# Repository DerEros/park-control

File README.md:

# park-control
A park distance control for my garage based on ESP8266

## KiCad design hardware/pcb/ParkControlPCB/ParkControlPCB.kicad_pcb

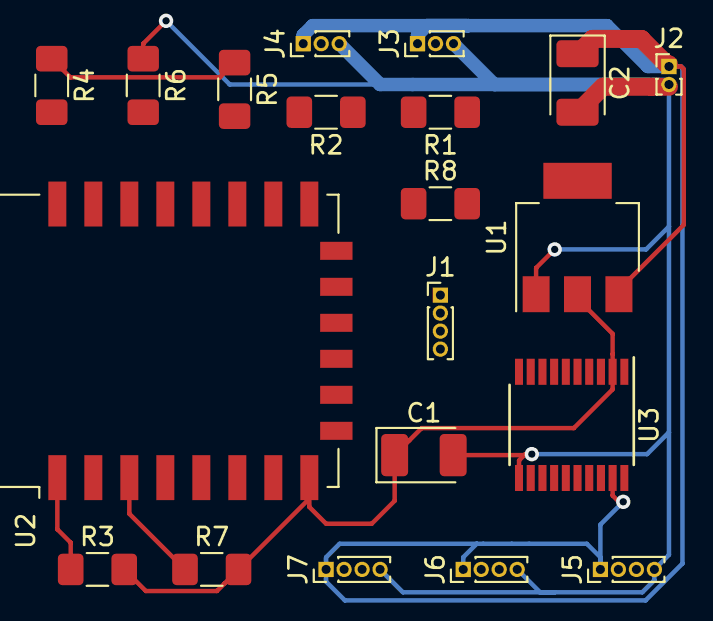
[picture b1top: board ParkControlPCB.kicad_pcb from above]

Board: 2 copper layers, 20 parts (0 on the bottom side), 27 nets.

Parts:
C1: 100 μF; CP_EIA-3528-12_Kemet-T_Pad1.50x2.35mm_HandSolder
C2: 1000 uF, 6,3V; CP_EIA-3528-12_Kemet-T_Pad1.50x2.35mm_HandSolder
J1: Prog; PinHeader_1x04_P1.00mm_Vertical
J2: PWR; PinHeader_1x02_P1.00mm_Vertical
J3: LED1; PinHeader_1x03_P1.00mm_Vertical
J4: LED2; PinHeader_1x03_P1.00mm_Vertical
J5: US1; PinHeader_1x04_P1.00mm_Vertical
J6: US2; PinHeader_1x04_P1.00mm_Vertical
J7: US3; PinHeader_1x04_P1.00mm_Vertical
R1, R2: 470; R_1206_3216Metric_Pad1.42x1.75mm_HandSolder
R3, R4, R5, R6, R7, R8: 10K; R_1206_3216Metric_Pad1.42x1.75mm_HandSolder
U1: LM1117-3.3; SOT-223
U2: ESP-12F; ESP-12E
U3: TXS0108EPW; TSSOP-20_4.4x6.5mm_P0.65mm

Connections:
/3V3: C1.1, R3.2, R4.1, R5.1, R7.2, U1.2, U2.8, U3.2
/DIN_LED_1: R1.1, U3.20
/DIN_LED_2: R2.1, U3.18
/LED_1: U2.22, U3.1
/LED_2: U2.21, U3.3
/MISO: J1.2, U2.10
/MOSI: J1.3, U2.13
/OE: R8.1, U2.4, U3.10
/SCK: J1.1, U2.14
/SS: J1.4, U2.9
/US_E_1: U2.20, U3.5
/US_E_1_5V: J5.3, U3.16
/US_E_2: U2.7, U3.7
/US_E_2_5V: J6.3, U3.14
/US_T_1: U2.19, U3.4
/US_T_1_5V: J5.2, U3.17
/US_T_2: U2.6, U3.6
/US_T_2_5V: J6.2, U3.15
GND: C1.2, C2.2, J2.2, J3.3, J4.3, J5.4, J6.4, J7.4, R6.1, R8.2, U1.1, U2.15, U3.11
unnamed: J3.2, R1.2
unnamed: J4.2, R2.2
unnamed: R3.1, U2.1
unnamed: R4.2, U2.18
unnamed: R5.2, U2.17
unnamed: R6.2, U2.16
unnamed: R7.1, U2.3
VCC: C2.1, J2.1, J3.1, J4.1, J5.1, J6.1, J7.1, U1.3, U3.19

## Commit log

2019-09-14 Add Makefile and entry .ino file
2019-09-14 Add logging library
2019-09-14 Ignore compile_commands.json
    It's local compiler settings, we don't want to share this
2019-09-14 Add NeoPixel library
    Had to delete the examples subdirectory in the library as the Makefile
    tries to build the examples and fails due to missing Bluetooth
    dependencies
2019-09-14 Add some LED demo code to test connection
2019-09-15 Switch ESP toolchain
    Using newest version from Master instead of the one packaged with
    Arduino IDE since the ESP Makefile just got a fix that only works with
    the latest toolchain.
2019-09-15 Add basic blink animation
    Not actually blinking yet. Just the scaffold for the actual code
2019-09-15 Add simple blink application
    Adding pixel patterns, animation and rederer classes. Also for testing a
    default animation build that generates a simple red/blue blinken app
2019-09-17 Start PCB hardware schema in KiCad
2019-09-17 Replace Adafruit_NeoPixel with FastLED
    Initial commit. Builds, not yet tested with hardware.
2019-09-17 Add power regulator and output capacitor
2019-09-18 Add power section to schematics
2019-09-18 Fix use of FastLED
    Now actually tested and working
2019-09-19 Attempt at using a switch to turn off blink at runtime
    Not yet successful
2019-09-24 Add power, spi, led and level shifter
2019-09-25 Added remaining pieces to schematics
2019-09-26 Add net class for 4A conduits
2019-09-26 Compact parts placement
2019-09-26 Some of the power circuits added
2019-09-29 Add handling for OE channel on logic level shifter
    Also: remove handling for push button - didn't work anyway.
2019-09-29 Fix missing pull-down on txs0108 OE pin
2019-09-29 Moved PIN definition to separate header
2019-09-29 Fixed number of LEDs
2019-09-29 Start class for distance measurement
2019-09-30 Add Ultrasonic library
    For ultrasound distance measurement
2019-09-30 Implement distance measurement
2019-09-30 Commit missing change
2019-10-02 Use interrupt based distance measurement
    To avoid blocking for many ms.
2019-10-03 Refactorings and code cleanup
2019-10-03 Introduce repeating pixel patterns
    Decorator class that can be wrapped around other patterns and will
    repeat the pattern continuously until eternity (UINT_MAX...).
2019-10-03 Start slide animation
    Knight-rider like animation where a pattern would contiuously move from
    the left to the right or vice-versa. Works best with
    RepeatingPixelPattern.
2019-10-03 Add SegmentPattern
    Supports patterns that are composed of multiple segments with a
    different color each. Segment size is flexible.
2019-10-03 Fix SlideAnimation
2019-10-03 Minor refactoring
2019-10-04 Add frame based animation and conditional animation
2019-10-04 [broken] Move blink animation to frame based base class
2019-10-04 Fixed typo
2019-10-04 Fix missing return statement
2019-10-04 Move SlideAnimation to frame based animation
2019-10-04 Start conditional animation
2019-10-05 Simplify use of conditional animation
2019-10-05 Introduce Stateful Animations
    This better reflects that animations can depend on a certain program
    state
2019-10-05 Add RangeCombineAnimation
    It can run multiple animations at the same time in different pixel
    ranges
2019-10-05 Embed ranged animation in conditional animation
2019-10-05 Add second ranged animation to conditional animation
2019-10-06 Move clock handling to separate class
2019-10-06 Move some files, add config and state
    Move app specific files to app folder. Clock becomes a reusable utility
    class and actually works now as it should.
    Config class that stores user configurable settings. Hard coded for now.
    State class encapsulates application state.
2019-10-06 Add FastLED template instances, fix last LED
    Last LED was always turned off when range was set correclty. Fixed the
    issue.
    Also added template instances for all relevant animation/pattern classes
    that work for the FastLED CRGB type.
2019-10-06 Encapsulate app specific code
    App specific code now moved to app folder. Specific animation builder
    for Park Control now available.
2019-10-06 Wire distance measure to state and fix crashes
2019-10-06 Fix synchronization issue with combined slide animations
2019-10-06 Start networking code
2019-10-06 Start basic config API
2019-10-09 Add REST calls to turn animation on/off
2019-10-09 Attempt at serving static files via HTTP
    Not working yet. SPIFFS seems to remain empty.
2019-10-10 Remove debug code
    The issue is within the ESP make file. When esptool is not found in the
    PATH it does not set the correct upload command. Instead of the SPI FS
    it simply uploads the app.
2019-10-10 Add JavaScript to web frontend
2019-10-11 Add Webpack
2019-10-11 Move web ui sources to new location
2019-10-12 Move to auto-generated HTML
2019-10-12 Implement dev-server mode, add materialize css
2019-10-12 Include materialize css into build
2019-10-12 Enable HTML fragments, Materialize JS components and icons
2019-10-12 Create components dir, add grid layout
2019-10-12 Split config into dev and prod
2019-10-12 Introduce jQuery and add On/Off card
2019-10-13 Move on/off functionality to switch widget
2019-10-13 Add REST call to on/off component
2019-10-13 Load initial state of park controle via REST API
    This allows to preinitialize the on/off switch with the correct state
2019-10-13 Reduce log level
2019-10-13 Turn off now does not leave LEDs on
2019-10-13 Add card to manage minimum distances
2019-10-14 Remove use of Serial.print
2019-10-14 Add tasks to build UI via Makefile
2019-10-14 Add flash_ui target to directly copy UI to device
2019-10-14 Add ArduinoJson library
2019-10-14 Add handling of JSON for setting new distances
2019-10-14 Introduce GZ mode for static files
2019-10-15 Attempt to use PEAP based WiFi authentication
    Not successful yet
2019-10-15 Write newly received distance config to file
2019-10-15 Add reading of distances config file
    When it does not exist, default values are sent
2019-10-15 Fix handling of GZip files
2019-10-15 Some fixes around sending distances to backend
2019-10-16 Minor changes for easier flashing and more debug out
2019-10-16 Fix backend not storing all distances
2019-10-16 Start implementation for reading distance settings at startup
    Also, restart after changing distance settings in order to re-read them
2019-10-17 Fixed storing and loading of distances
2019-10-17 Switch ConditionalAnimation to use std::function
    Instead of function pointers
2019-10-17 Fix use of loaded distance config
2019-10-17 Add detection of movement
    Deactivate LEDs after 5s without movement, activate on first sign of
    movement
2019-10-18 Add builder for halloween animation
2019-10-18 Fix compiler error
2019-10-19 Add option to select between park control and halloween mode
2019-10-19 Halloween mode is now activated on boot
2019-10-19 First shot at candle flicker
2019-10-19 Improved flicker looks
2019-10-20 Enabled animation mode selection over Web UI
2019-10-20 Add Spooky mode for halloween animation
2019-10-20 Improved colors of animations
2019-10-20 Reactivate distance measurement
    Seems to be interfering with SPIFFS startup (which occasionally crashes)
